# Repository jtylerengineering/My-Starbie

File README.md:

# My-Starbie

# Description
The Starbie is a starter project for Half-Life Week 1. The project is a small interactive desktop pet powered by the Seeed Studio Xiao ESP32 C3 microcontroller. The original project has been augmented  by adding a piezo buzzer and changing the original 'Run' interaction to a 'Sing' interaction.  

# Getting Started
## Prerequesites

### Hardware
 You will also need to obtain the PCB. For the Gerber flies, head to <a href=" ">Gerber Files</a>. Other than that, you will need a soldering iron and solder to wire the components to the board. The table below is based on the components I used while designing this.
 
> [!NOTE]
> refer to Starbie BOM - Sheet 1.csv instead of Bom.csv to get an accurate count. Bom.csv is a result of the Half Life site's system, and is inaccurate to a full project.

| Component | Amount | Price (USD) | Link |
| --- | --- | --- | --- |
| Seeed Studio XIAO ESP32-C3 | 1 | $9.36 | <a href="https://www.aliexpress.us/item/3256807240718259.html?spm=a2g0o.productlist.0.0.33dd7473O64Rzo&mp=1&pdp_npi=6%40dis%21USD%21USD+9.36%21USD+5.36%21%21USD+5.36%21%21%21%402103094f17925851627315813e0e41%2112000040716079484%21ct%21US%218282019388%21%211%210%21&gatewayAdapt=glo2usa"> Aliexpress</a> |
| 10 kOhm Potentiometer | 1 | $0.11 | <a href= "https://www.alibaba.com/product-detail/PT10-10K-spain-potentiometer-B103_1600210333807.html">Alibaba</a> |
| 0.96 inch OLED Display | 1 | $2.78 | <a href="https://www.aliexpress.us/item/3256805954920554.html?spm=a2g0o.detail.0.0.73aa0SRG0SRG6m&mp=1&pdp_npi=6%40dis%21USD%21USD+2.78%21USD+1.09%21%21USD+1.09%21%21%21%402103117b17925861781885228e0d09%2112000035944225406%21ct%21US%218282019388%21%211%210%21&_gl=1*1veh4cy*_gcl_aw*R0NMLjE3OTE3Mjc2NjYuQ2p3S0NBanc1NnpXQmhCMEVpd0FkUE9RT2RLQnpWQTdQcnZsamVPZG4wN2ozaWRWVmZHLXhPNldWM1VNSnRFUW9aVGVzRElPT3pCbDhSb0MyS2dRQXZEX0J3RQ..*_gcl_dc*R0NMLjE3OTE3Mjc2NjYuQ2p3S0NBanc1NnpXQmhCMEVpd0FkUE9RT2RLQnpWQTdQcnZsamVPZG4wN2ozaWRWVmZHLXhPNldWM1VNSnRFUW9aVGVzRElPT3pCbDhSb0MyS2dRQXZEX0J3RQ..*_gcl_au*MTY3NjU0OTcyNi4xNzkxNzI3NjA3*_ga*MTc2OTQzNzcxNTAzOTIzMS4xNzkxNzIyNjI4Mjk3*_ga_VED1YSGNC7*czE3OTI1ODUxNzYkbzUkZzEkdDE3OTI1ODYxODUkajUyJGwwJGgw&gatewayAdapt=glo2usa">Aliexpress</a> |
| Keyboard Switches | 1 set | $0.65 | <a href="https://www.aliexpress.us/item/3256806385705423.html?spm=a2g0o.detail.0.0.2868xZNxxZNxV6&mp=1&pdp_npi=6%40dis%21USD%21USD+0.65%21USD+0.47%21%21USD+0.47%21%21%21%402103117b17925861851965563e0d09%2112000037704740809%21ct%21US%218282019388%21%211%210%21&_gl=1*103ies4*_gcl_aw*R0NMLjE3OTE3Mjc2NjYuQ2p3S0NBanc1NnpXQmhCMEVpd0FkUE9RT2RLQnpWQTdQcnZsamVPZG4wN2ozaWRWVmZHLXhPNldWM1VNSnRFUW9aVGVzRElPT3pCbDhSb0MyS2dRQXZEX0J3RQ..*_gcl_dc*R0NMLjE3OTE3Mjc2NjYuQ2p3S0NBanc1NnpXQmhCMEVpd0FkUE9RT2RLQnpWQTdQcnZsamVPZG4wN2ozaWRWVmZHLXhPNldWM1VNSnRFUW9aVGVzRElPT3pCbDhSb0MyS2dRQXZEX0J3RQ..*_gcl_au*MTY3NjU0OTcyNi4xNzkxNzI3NjA3*_ga*MTc2OTQzNzcxNTAzOTIzMS4xNzkxNzIyNjI4Mjk3*_ga_VED1YSGNC7*czE3OTI1ODUxNzYkbzUkZzEkdDE3OTI1ODYzNjYkajYwJGwwJGgw&gatewayAdapt=glo2usa">Aliexpress</a> |
| MPU6050 Tilt Sensor | 1 | $2.10 | <a href="https://www.aliexpress.us/item/3256809871479525.html?spm=a2g0o.productlist.main.2.52804922fHav3E&algo_pvid=0fbeef62-7378-48a1-adb1-371e169a90af&algo_exp_id=0fbeef62-7378-48a1-adb1-371e169a90af-1&pdp_ext_f=%7B%22order%22%3A%223447%22%2C%22eval%22%3A%221%22%2C%22fromPage%22%3A%22search%22%7D&pdp_npi=6%40dis%21USD%212.10%211.09%21%21%212.10%211.09%21%402101d3fe17917546524812582e10eb%2112000050979433010%21sea%21US%218282019388%21ABX%211%210%21n_tag%3A-29910%3Bd%3Af35780dd%3Bm03_new_user%3A-29895%3BpisId%3A5000000218032551&curPageLogUid=ErNcXavS6G41&utparam-url=scene%3Asearch%7Cquery_from%3A%7Cx_object_id%3A1005010057794277%7C_p_origin_prod%3A">Aleiexpress</a> |
| Piezo Buzzer | 1 | $1.90 | <a href="https://www.aliexpress.us/item/3256807978776593.html?spm=a2g0o.productlist.main.4.68504059USJBKe&aem_p4p_detail=202610210545177614210076402460000779104&algo_pvid=b9cfe003-73af-4c05-a8ab-92390f81b2b9&algo_exp_id=b9cfe003-73af-4c05-a8ab-92390f81b2b9-3&pdp_ext_f=%7B%22order%22%3A%22133%22%2C%22eval%22%3A%221%22%2C%22fromPage%22%3A%22search%22%7D&pdp_npi=6%40dis%21USD%211.90%211.90%21%21%2112.63%2112.63%21%4021032e4e17925867176664384e0e2b%2112000044055302230%21sea%21US%218282019388%21ABX%211%210%21n_tag%3A-29910%3Bd%3Accb82ee9%3Bm03_new_user%3A-29895&curPageLogUid=14ANKVOokQq1&utparam-url=scene%3Asearch%7Cquery_from%3A%7Cx_object_id%3A1005008165091345%7C_p_origin_prod%3A&search_p4p_id=202610210545177614210076402460000779104_1">Aliexpress</a> |
| DHT11 Environment Sensor | 1 | $5.76 | <a href="https://www.aliexpress.us/item/3256809040855978.html?spm=a2g0o.productlist.main.2.5337604arbm8Gt&algo_pvid=8c74fd26-a937-4906-9cb9-6d6c3bbb966c&algo_exp_id=8c74fd26-a937-4906-9cb9-6d6c3bbb966c-1&pdp_ext_f=%7B%22order%22%3A%22203%22%2C%22eval%22%3A%221%22%2C%22fromPage%22%3A%22search%22%7D&pdp_npi=6%40dis%21USD%215.75%215.75%21%21%2138.18%2138.18%21%402103128817925877811354370e0ea1%2112000048385025197%21sea%21US%218282019388%21ABX%211%210%21n_tag%3A-29910%3Bd%3Accb82ee9%3Bm03_new_user%3A-29895&curPageLogUid=QFI6nGCRqfPS&utparam-url=scene%3Asearch%7Cquery_from%3A%7Cx_object_id%3A1005009227170730%7C_p_origin_prod%3A">Aliexpress</a> |
| 10 kOhm resister | 1 | $0.14 | <a href="https://www.jameco.com/z/CF1W103JRC-Jameco-ValuePro-Resistor-Carbon-Film-10k-Ohm-1-Watt-5-_2237221.html?srsltid=AU7gw4UA99z_8AuIH1aGr_tBybTi_9l5eX-QZ8F5XKKPQdWzRGTRjFpqPhA">Jameco</a> |
| PCB | 1 | $1.88 | <a href="https://jlcpcb.com/">JLPCB</a> | 
| Shipping/Fees | $17.36 |
| Total | $47.69 |

### Software
You will need to have the Arduino IDE installed in order to edit and upload any and all code to the Starbie. If you wish to change the PCB, you will need to have Kicad installed.

## Wiring

As of now, I have not printed the board. I will probably not be able to add a build tutorial until Week Six, as to put images here. However, I can at least discuss how the sound system is wired up.

The simple explanation is that the potentiometer is wired to Digital Pin 7 on the XIAO board. This is where the input voltage is. Then the positive lead on the buzzer is wired into the wiper pin of the potentiometer. Both components are grounded using a ground pool on the PCB.

## Installing Firmware
To download the firmware for the Starbie, go to <a href="https://github.com/jtylerengineering/My-Starbie/blob/main/Starbie_firmware/Starbie.ino">Starbie.ino</a>.

### Settings
An explanation for setting up for an upload will be added during week six.

### the Sing() Function
One of the changes I made to the original project was adding the ability to play a song. As of now, you will only be able to play one line and note at a time (if you want more than this, you will need to add more piezo buzzers). However, I did lay down the framework for putting your own song instead of my example. 

First off, the notes shown above are all in C Major, so you will need to either find a song in that key or adjust the frequencies accordingly. The syntax for writing a note into the code is as follows:
     ` tone(buzzerPin, note); `

This mostly translates to 'I want my piezo to play this note'. To change the duration of the note you would use `delay(beat * time)` The "time" here is how many beats this would be. This also applies to rests, but you would just use Arduino's `noTone()` function there.

# License
this project is not under any sort of license.

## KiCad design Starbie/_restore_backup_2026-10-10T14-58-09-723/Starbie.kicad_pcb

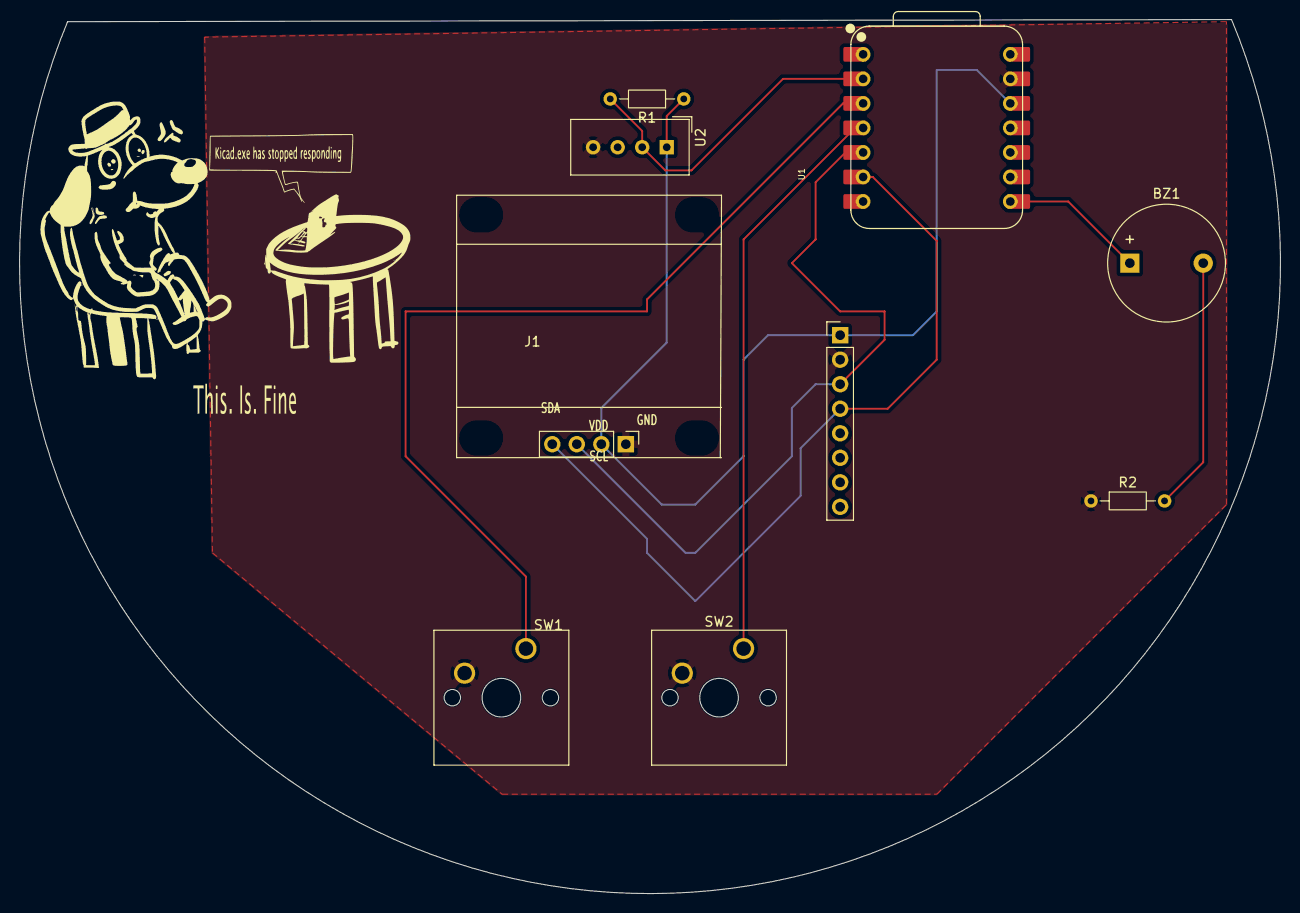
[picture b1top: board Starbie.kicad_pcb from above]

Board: 2 copper layers, 130.6 x 90.5 mm, 9 parts (0 on the bottom side), 9 nets.

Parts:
BZ1: Buzzer; Buzzer_12x9.5RM7.6
J1: Conn_01x04_Pin; Display_128x64_096_I2C
J2: Conn_01x08_Pin; PinHeader_1x08_P2.54mm_Vertical
R1: 10k; R_Axial_DIN0204_L3.6mm_D1.6mm_P7.62mm_Horizontal
R2: 100; R_Axial_DIN0204_L3.6mm_D1.6mm_P7.62mm_Horizontal
SW1, SW2: SW_Push; SW_Cherry_MX_1.00u_PCB
U1: XIAO-ESP32-C3-SMD; XIAO-ESP32-C6-DIP
U2: DHT11; Aosong_DHT11_5.5x12.0_P2.54mm

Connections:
+3.3V: J1.2, J2.1, R1.1, U1.12 (3V3_OUT), U2.1 (VDD)
/DHT11 DATA: R1.2, U1.2 (D1), U2.2 (DATA)
/GPIO 2: SW1.1, U1.3 (D2)
/GPIO 3: SW2.1, U1.4 (D3)
/GPIO 20: BZ1.1 (+), U1.8 (D7)
/SCL: J1.3, J2.3, U1.5 (D4)
/SDA: J1.4, J2.4, U1.6 (D5)
GND: J1.1, J2.2, R2.1, SW1.2, SW2.2, U1.13 (GND), U2.4 (GND)
unnamed: BZ1.2 (-), R2.2
